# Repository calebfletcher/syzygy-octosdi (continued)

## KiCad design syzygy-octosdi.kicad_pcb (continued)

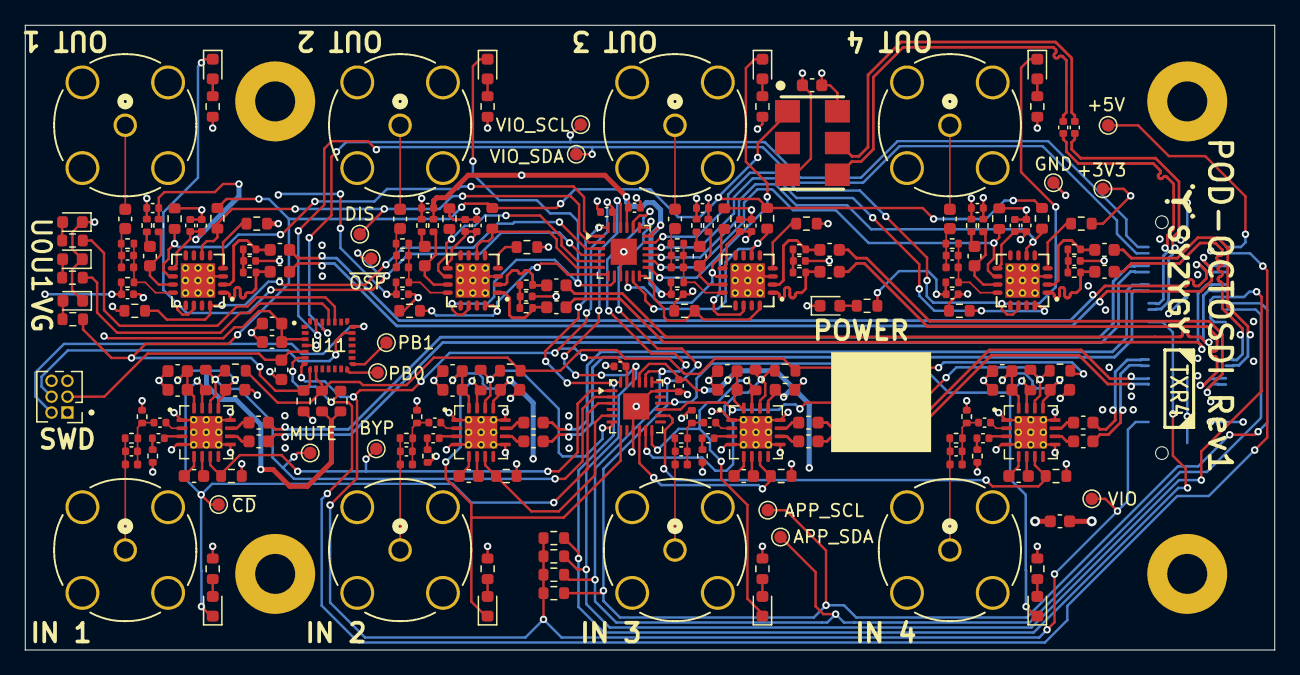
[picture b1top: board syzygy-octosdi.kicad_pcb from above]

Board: 4 copper layers, 100.0 x 50.0 mm, 231 parts (1 on the bottom side), 152 nets.
